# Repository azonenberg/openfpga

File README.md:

# openfpga
Open-source FPGA/CPLD toolchain project for multiple device families.

The most mature target is Silego GreenPAK4. Active work is underway for Xilinx CoolRunner-II and Cypress PSoC5LP.

Questions? Comments? Having trouble getting it to work? Join our IRC, ##openfpga on Freenode.

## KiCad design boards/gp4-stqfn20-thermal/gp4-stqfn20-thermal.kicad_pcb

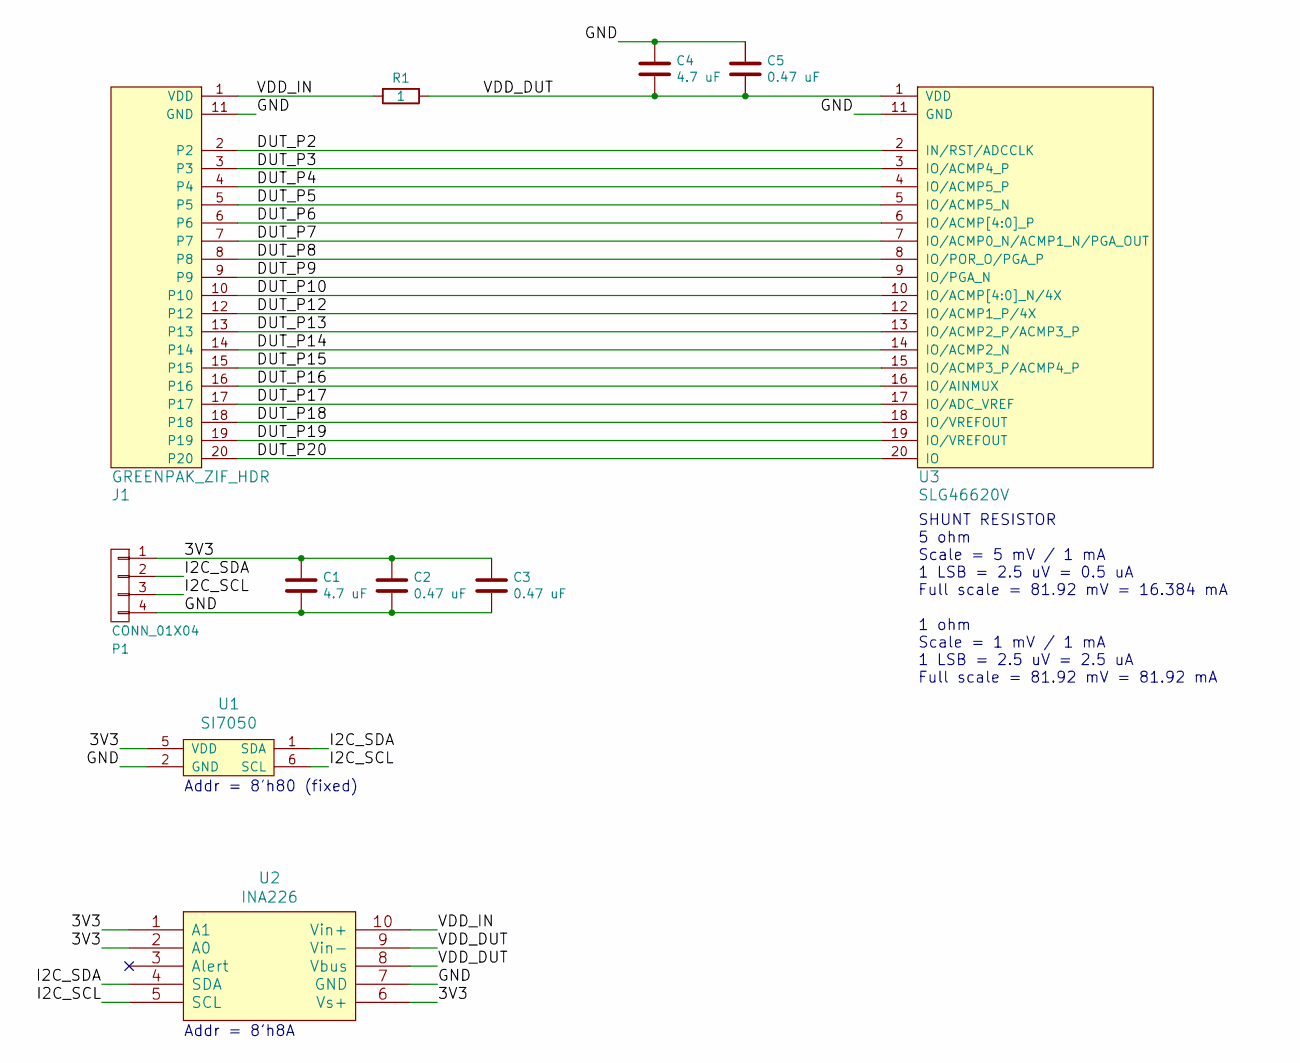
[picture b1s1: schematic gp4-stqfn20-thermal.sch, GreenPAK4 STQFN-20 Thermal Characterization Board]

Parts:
C1, C4: 4.7 uF; EIA_0603_CAP_NOSILK
C2, C3, C5: 0.47 uF; EIA_0402_CAP_NOSILK
J1: GREENPAK_ZIF_HDR; CONN_HEADER_2.54MM_2x10_RA_FEMALE
P1: CONN_01X04; CONN_HEADER_2.54MM_1x4
R1: 1; EIA_0805_CAP_NOSILK
U1: SI7050; DFN_6_1MM_3x3MM
U2: INA226; SOP_10_0.5MM_3MM
U3: SLG46620V; QFN_20_0.4MM_3x2MM_SILEGO_STQFN

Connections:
/3V3: C1.1, C2.1, C3.1, P1.1, U1.5 (VDD), U2.1 (A1), U2.2 (A0), U2.6 (Vs+)
/DUT_P2: J1.2, U3.2 (IN/RST/ADCCLK)
/DUT_P3: J1.3, U3.3 (IO/ACMP4_P)
/DUT_P4: J1.4, U3.4 (IO/ACMP5_P)
/DUT_P5: J1.5, U3.5 (IO/ACMP5_N)
/DUT_P6: J1.6, U3.6 (IO/ACMP[4:0]_P)
/DUT_P7: J1.7, U3.7 (IO/ACMP0_N/ACMP1_N/PGA_OUT)
/DUT_P8: J1.8, U3.8 (IO/POR_O/PGA_P)
/DUT_P9: J1.9, U3.9 (IO/PGA_N)
/DUT_P10: J1.10, U3.10 (IO/ACMP[4:0]_N/4X)
/DUT_P12: J1.12, U3.12 (IO/ACMP1_P/4X)
/DUT_P13: J1.13, U3.13 (IO/ACMP2_P/ACMP3_P)
/DUT_P14: J1.14, U3.14 (IO/ACMP2_N)
/DUT_P15: J1.15, U3.15 (IO/ACMP3_P/ACMP4_P)
/DUT_P16: J1.16, U3.16 (IO/AINMUX)
/DUT_P17: J1.17, U3.17 (IO/ADC_VREF)
/DUT_P18: J1.18, U3.18 (IO/VREFOUT)
/DUT_P19: J1.19, U3.19 (IO/VREFOUT)
/DUT_P20: J1.20, U3.20 (IO)
/GND: C1.2, C2.2, C3.2, C4.1, C5.1, J1.11 (GND), P1.4, U1.2 (GND), U2.7 (GND), U3.11 (GND)
/I2C_SCL: P1.3, U1.6 (SCL), U2.5 (SCL)
/I2C_SDA: P1.2, U1.1 (SDA), U2.4 (SDA)
/VDD_DUT: C4.2, C5.2, R1.1, U2.8 (Vbus), U2.9 (Vin-), U3.1 (VDD)
/VDD_IN: J1.1 (VDD), R1.2, U2.10 (Vin+)

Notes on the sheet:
Addr = 8'h80 (fixed)
Addr = 8'h8A
SHUNT RESISTOR 5 ohm Scale = 5 mV / 1 mA 1 LSB = 2.5 uV = 0.5 uA Full scale = 81.92 mV = 16.384 mA 1 ohm Scale = 1 mV / 1 mA 1 LSB = 2.5 uV = 2.5 uA Full scale = 81.92 mV = 81.92 mA

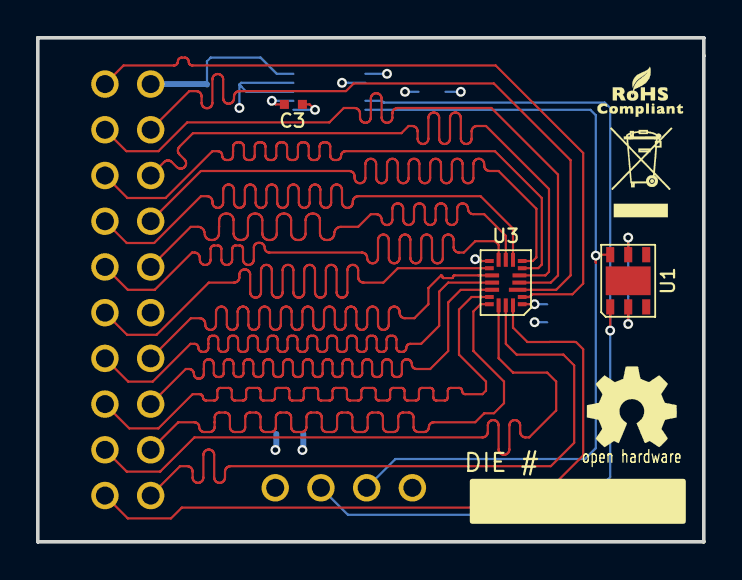
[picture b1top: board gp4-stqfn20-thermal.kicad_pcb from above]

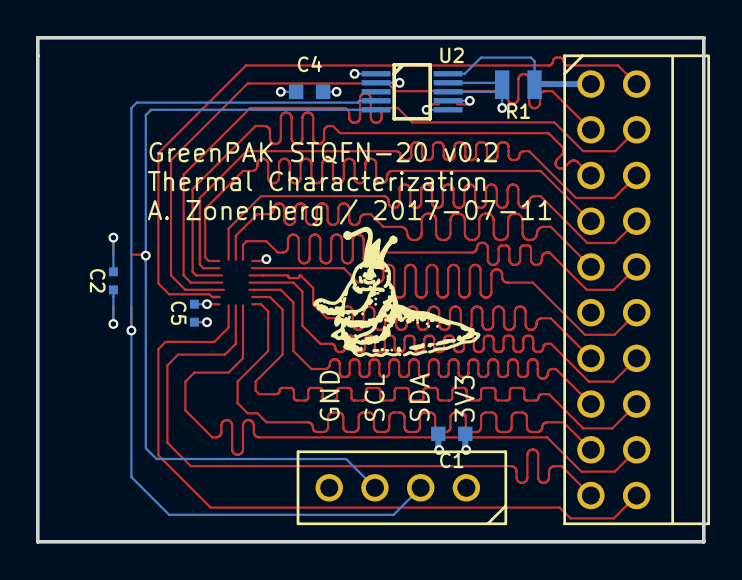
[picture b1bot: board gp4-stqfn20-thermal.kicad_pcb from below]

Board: 4 copper layers, 37.0 x 28.0 mm, 11 parts (8 on the bottom side), 24 nets.

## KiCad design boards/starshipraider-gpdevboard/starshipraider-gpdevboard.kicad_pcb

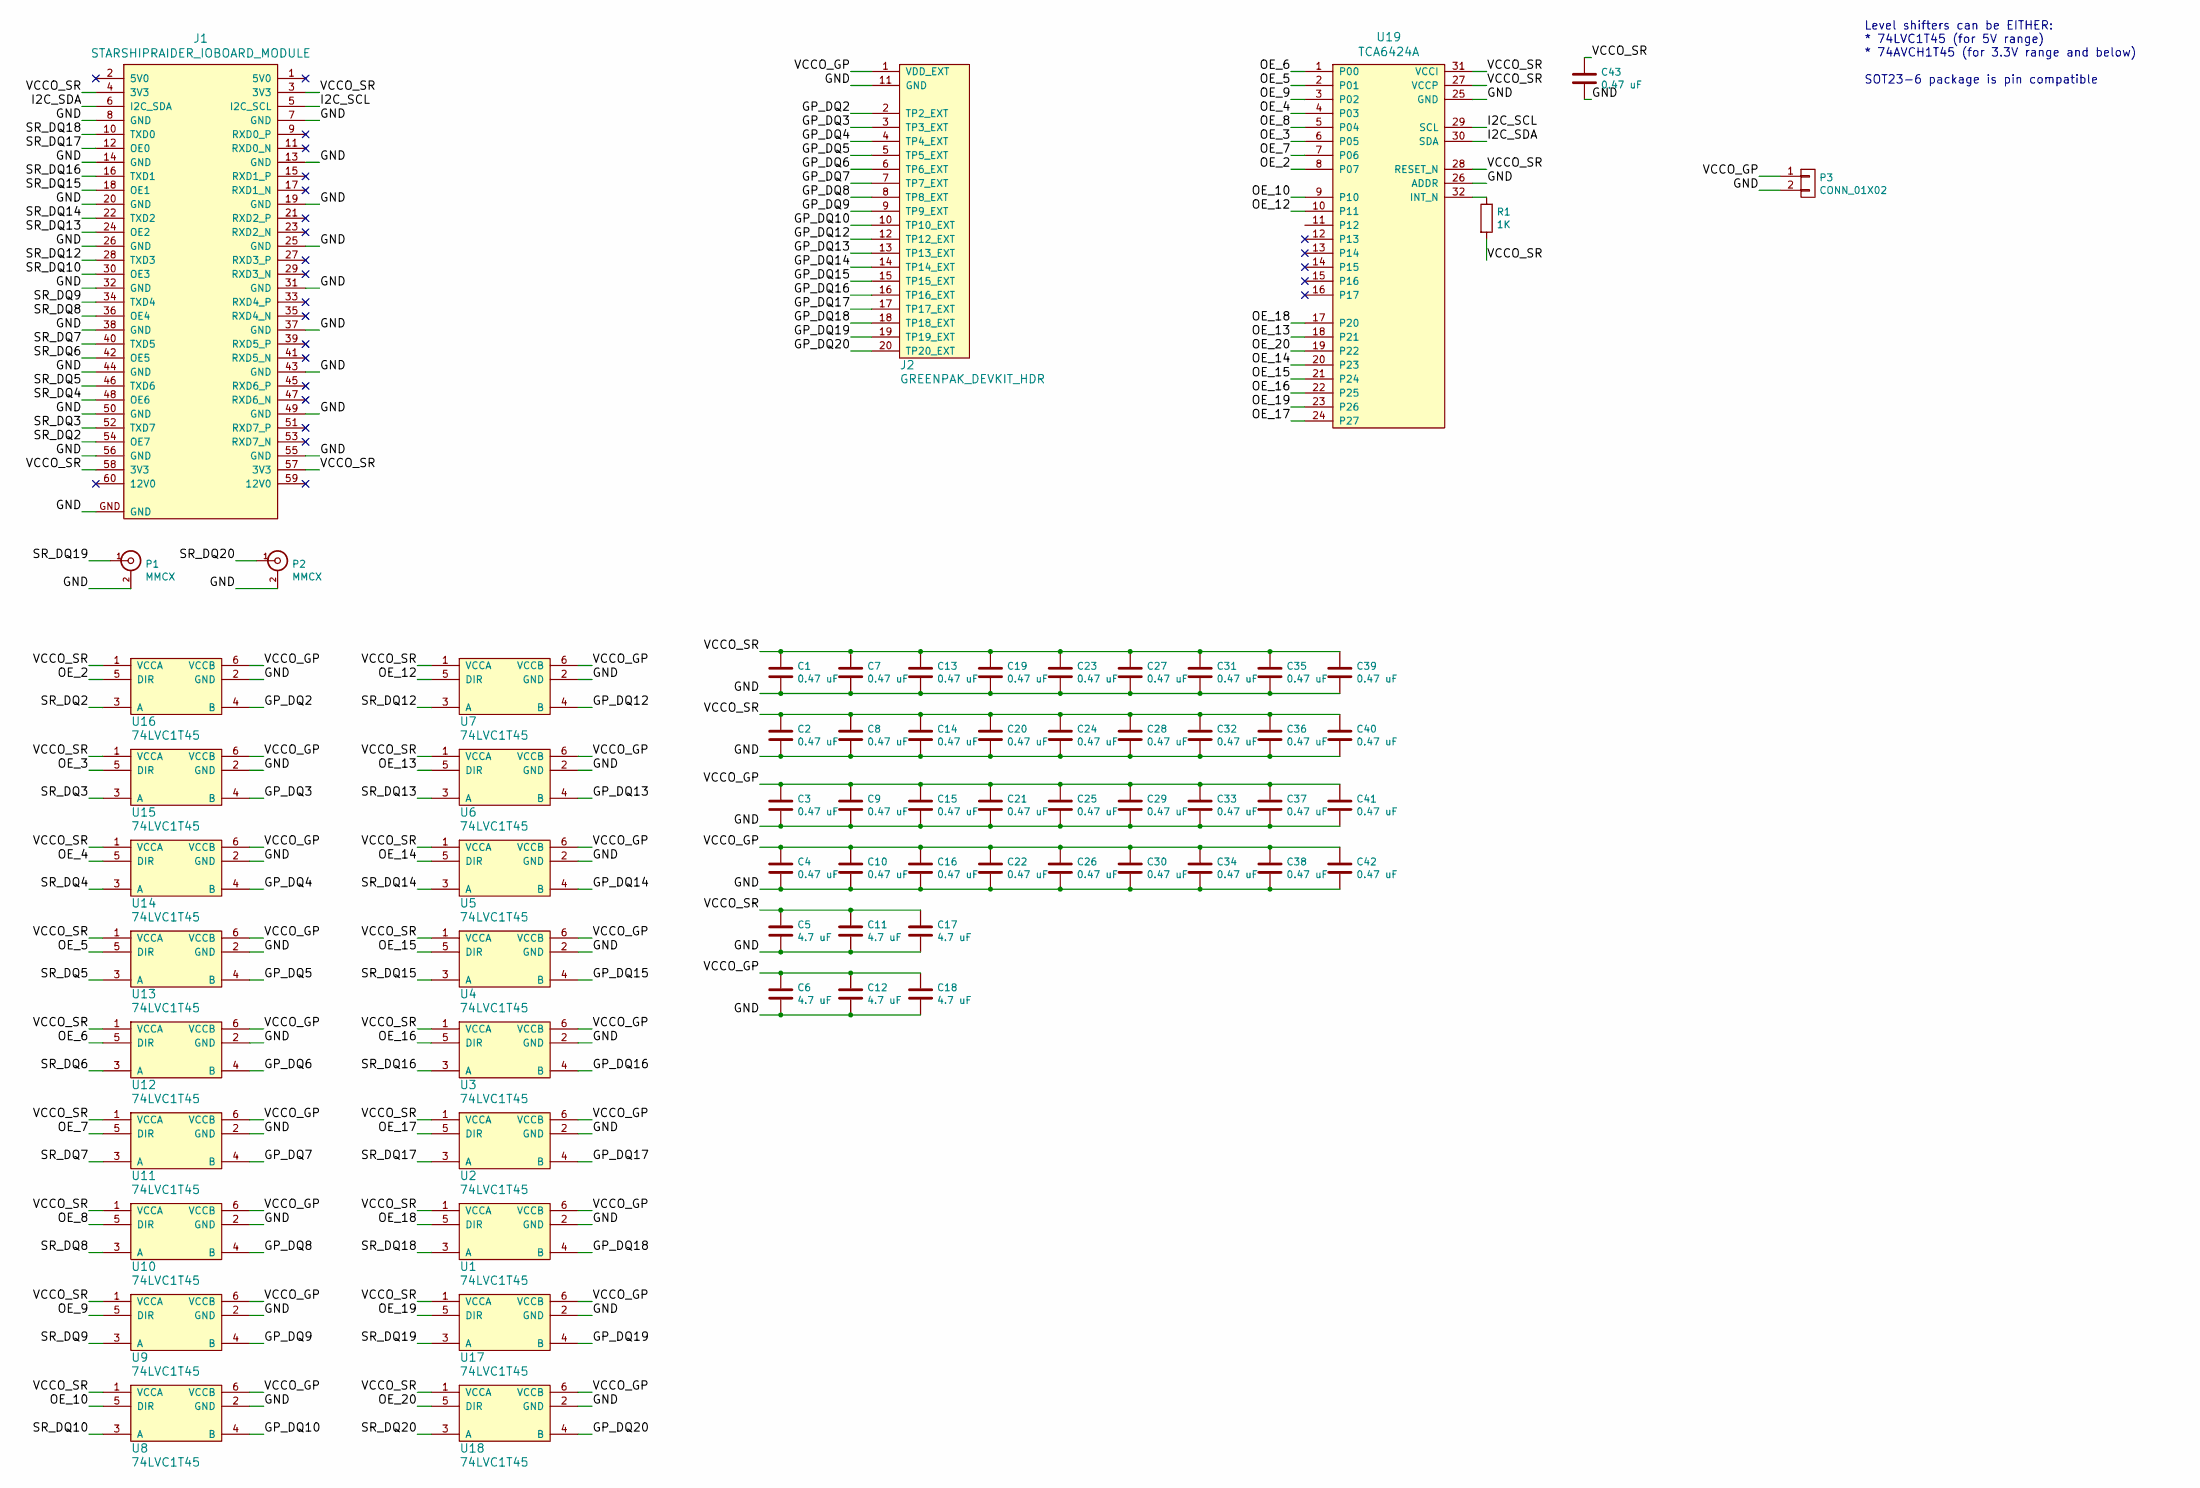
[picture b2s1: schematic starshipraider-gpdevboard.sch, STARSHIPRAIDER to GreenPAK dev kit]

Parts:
C1, C2, C3, C4, C7, C8, C9, C10, C13, C14, C15, C16, C19, C20, C21, C22, C23, C24, C25, C26, C27, C28, C29, C30, C31, C32, C33, C34, C35, C36, C37, C38, C39, C40, C41, C42, C43: 0.47 uF; EIA_0402_CAP_NOSILK
C5, C6, C11, C12, C17, C18: 4.7 uF; EIA_0603_CAP_NOSILK
J1: STARSHIPRAIDER_IOBOARD_MODULE; CONN_SAMTEC_QSH-030-01-L-D-A
J2: GREENPAK_DEVKIT_HDR; CONN_HEADER_2.54MM_2x10_RA_FEMALE
P1, P2: MMCX; CONN_MMCX_LINX_CONNMMCX002SMD
P3: CONN_01X02; CONN_HEADER_2.54MM_1x2
R1: 1K; EIA_0402_RES_NOSILK
U1, U2, U3, U4, U5, U6, U7, U8, U9, U10, U11, U12, U13, U14, U15, U16, U17, U18: 74LVC1T45; SOT23_6
U19: TCA6424A; QFN_32_0.5MM_5x5MM

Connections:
/GND: C1.2, C2.2, C3.2, C4.2, C5.2, C6.2, C7.2, C8.2, C9.2, C10.2, C11.2, C12.2, C13.2, C14.2, C15.2, C16.2, C17.2, C18.2, C19.2, C20.2, C21.2, C22.2, C23.2, C24.2, C25.2, C26.2, C27.2, C28.2, C29.2, C30.2, C31.2, C32.2, C33.2, C34.2, C35.2, C36.2, C37.2, C38.2, C39.2, C40.2, C41.2, C42.2, C43.2, J1.7 (GND), J1.8 (GND), J1.13 (GND), J1.14 (GND), J1.19 (GND), J1.20 (GND), J1.25 (GND), J1.26 (GND), J1.31 (GND), J1.32 (GND), J1.37 (GND), J1.38 (GND), J1.43 (GND), J1.44 (GND), J1.49 (GND), J1.50 (GND), J1.55 (GND), J1.56 (GND), J1.GND, J2.11 (GND), P1.2 (Ext), P2.2 (Ext), P3.2, U1.2 (GND), U2.2 (GND), U3.2 (GND), U4.2 (GND), U5.2 (GND), U6.2 (GND), U7.2 (GND), U8.2 (GND), U9.2 (GND), U10.2 (GND), U11.2 (GND), U12.2 (GND), U13.2 (GND), U14.2 (GND), U15.2 (GND), U16.2 (GND), U17.2 (GND), U18.2 (GND), U19.25 (GND), U19.26 (ADDR)
/GP_DQ2: J2.2 (TP2_EXT), U16.4 (B)
/GP_DQ3: J2.3 (TP3_EXT), U15.4 (B)
/GP_DQ4: J2.4 (TP4_EXT), U14.4 (B)
/GP_DQ5: J2.5 (TP5_EXT), U13.4 (B)
/GP_DQ6: J2.6 (TP6_EXT), U12.4 (B)
/GP_DQ7: J2.7 (TP7_EXT), U11.4 (B)
/GP_DQ8: J2.8 (TP8_EXT), U10.4 (B)
/GP_DQ9: J2.9 (TP9_EXT), U9.4 (B)
/GP_DQ10: J2.10 (TP10_EXT), U8.4 (B)
/GP_DQ12: J2.12 (TP12_EXT), U7.4 (B)
/GP_DQ13: J2.13 (TP13_EXT), U6.4 (B)
/GP_DQ14: J2.14 (TP14_EXT), U5.4 (B)
/GP_DQ15: J2.15 (TP15_EXT), U4.4 (B)
/GP_DQ16: J2.16 (TP16_EXT), U3.4 (B)
/GP_DQ17: J2.17 (TP17_EXT), U2.4 (B)
/GP_DQ18: J2.18 (TP18_EXT), U1.4 (B)
/GP_DQ19: J2.19 (TP19_EXT), U17.4 (B)
/GP_DQ20: J2.20 (TP20_EXT), U18.4 (B)
/I2C_SCL: J1.5 (I2C_SCL), U19.29 (SCL)
/I2C_SDA: J1.6 (I2C_SDA), U19.30 (SDA)
/OE_2: U16.5 (DIR), U19.8 (P07)
/OE_3: U15.5 (DIR), U19.6 (P05)
/OE_4: U14.5 (DIR), U19.4 (P03)
/OE_5: U13.5 (DIR), U19.2 (P01)
/OE_6: U12.5 (DIR), U19.1 (P00)
/OE_7: U11.5 (DIR), U19.7 (P06)
/OE_8: U10.5 (DIR), U19.5 (P04)
/OE_9: U9.5 (DIR), U19.3 (P02)
/OE_10: U8.5 (DIR), U19.9 (P10)
/OE_12: U7.5 (DIR), U19.10 (P11)
/OE_13: U6.5 (DIR), U19.18 (P21)
/OE_14: U5.5 (DIR), U19.20 (P23)
/OE_15: U4.5 (DIR), U19.21 (P24)
/OE_16: U3.5 (DIR), U19.22 (P25)
/OE_17: U2.5 (DIR), U19.24 (P27)
/OE_18: U1.5 (DIR), U19.17 (P20)
/OE_19: U17.5 (DIR), U19.23 (P26)
/OE_20: U18.5 (DIR), U19.19 (P22)
/SR_DQ2: J1.54 (OE7), U16.3 (A)
/SR_DQ3: J1.52 (TXD7), U15.3 (A)
/SR_DQ4: J1.48 (OE6), U14.3 (A)
/SR_DQ5: J1.46 (TXD6), U13.3 (A)
/SR_DQ6: J1.42 (OE5), U12.3 (A)
/SR_DQ7: J1.40 (TXD5), U11.3 (A)
/SR_DQ8: J1.36 (OE4), U10.3 (A)
/SR_DQ9: J1.34 (TXD4), U9.3 (A)
/SR_DQ10: J1.30 (OE3), U8.3 (A)
/SR_DQ12: J1.28 (TXD3), U7.3 (A)
/SR_DQ13: J1.24 (OE2), U6.3 (A)
/SR_DQ14: J1.22 (TXD2), U5.3 (A)
/SR_DQ15: J1.18 (OE1), U4.3 (A)
/SR_DQ16: J1.16 (TXD1), U3.3 (A)
/SR_DQ17: J1.12 (OE0), U2.3 (A)
/SR_DQ18: J1.10 (TXD0), U1.3 (A)
/SR_DQ19: P1.1 (In), U17.3 (A)
/SR_DQ20: P2.1 (In), U18.3 (A)
/VCCO_GP: C3.1, C4.1, C6.1, C9.1, C10.1, C12.1, C15.1, C16.1, C18.1, C21.1, C22.1, C25.1, C26.1, C29.1, C30.1, C33.1, C34.1, C37.1, C38.1, C41.1, C42.1, J2.1 (VDD_EXT), P3.1, U1.6 (VCCB), U2.6 (VCCB), U3.6 (VCCB), U4.6 (VCCB), U5.6 (VCCB), U6.6 (VCCB), U7.6 (VCCB), U8.6 (VCCB), U9.6 (VCCB), U10.6 (VCCB), U11.6 (VCCB), U12.6 (VCCB), U13.6 (VCCB), U14.6 (VCCB), U15.6 (VCCB), U16.6 (VCCB), U17.6 (VCCB), U18.6 (VCCB)
/VCCO_SR: C1.1, C2.1, C5.1, C7.1, C8.1, C11.1, C13.1, C14.1, C17.1, C19.1, C20.1, C23.1, C24.1, C27.1, C28.1, C31.1, C32.1, C35.1, C36.1, C39.1, C40.1, C43.1, J1.3 (3V3), J1.4 (3V3), J1.57 (3V3), J1.58 (3V3), R1.2, U1.1 (VCCA), U2.1 (VCCA), U3.1 (VCCA), U4.1 (VCCA), U5.1 (VCCA), U6.1 (VCCA), U7.1 (VCCA), U8.1 (VCCA), U9.1 (VCCA), U10.1 (VCCA), U11.1 (VCCA), U12.1 (VCCA), U13.1 (VCCA), U14.1 (VCCA), U15.1 (VCCA), U16.1 (VCCA), U17.1 (VCCA), U18.1 (VCCA), U19.27 (VCCP), U19.28 (RESET_N), U19.31 (VCCI)
unnamed: R1.1, U19.32 (INT_N)

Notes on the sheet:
Level shifters can be EITHER: * 74LVC1T45 (for 5V range) * 74AVCH1T45 (for 3.3V range and below) SOT23-6 package is pin compatible

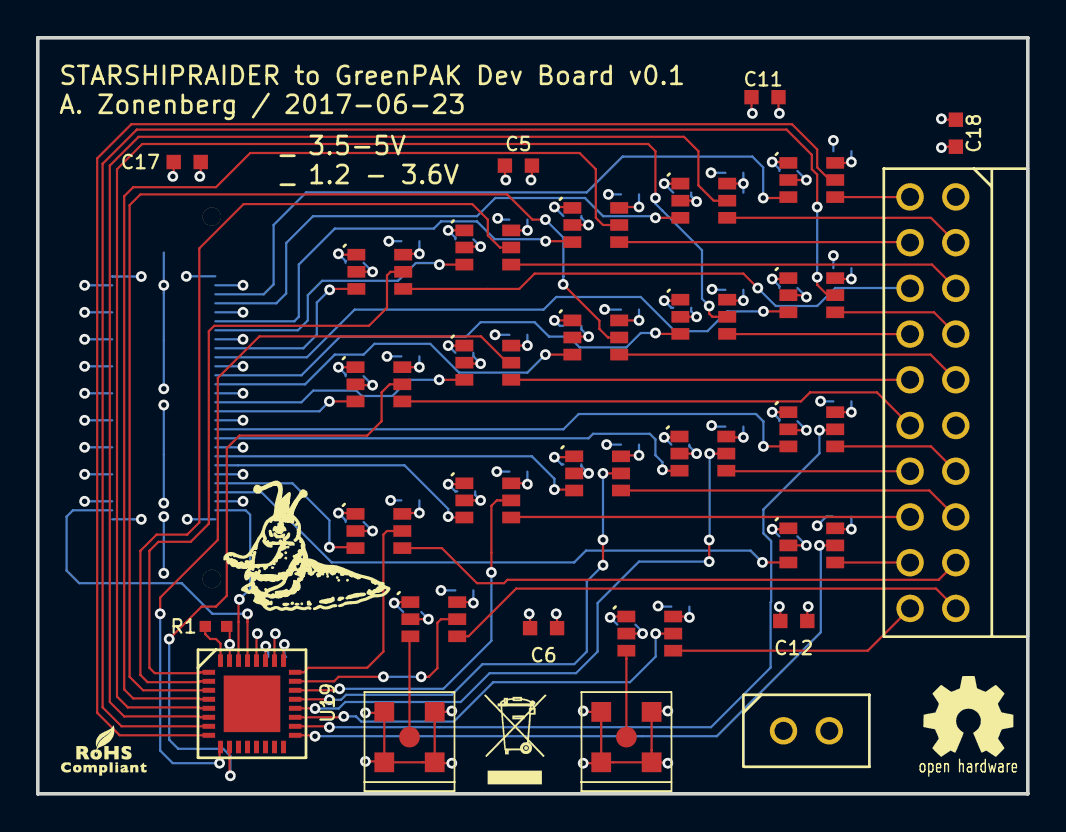
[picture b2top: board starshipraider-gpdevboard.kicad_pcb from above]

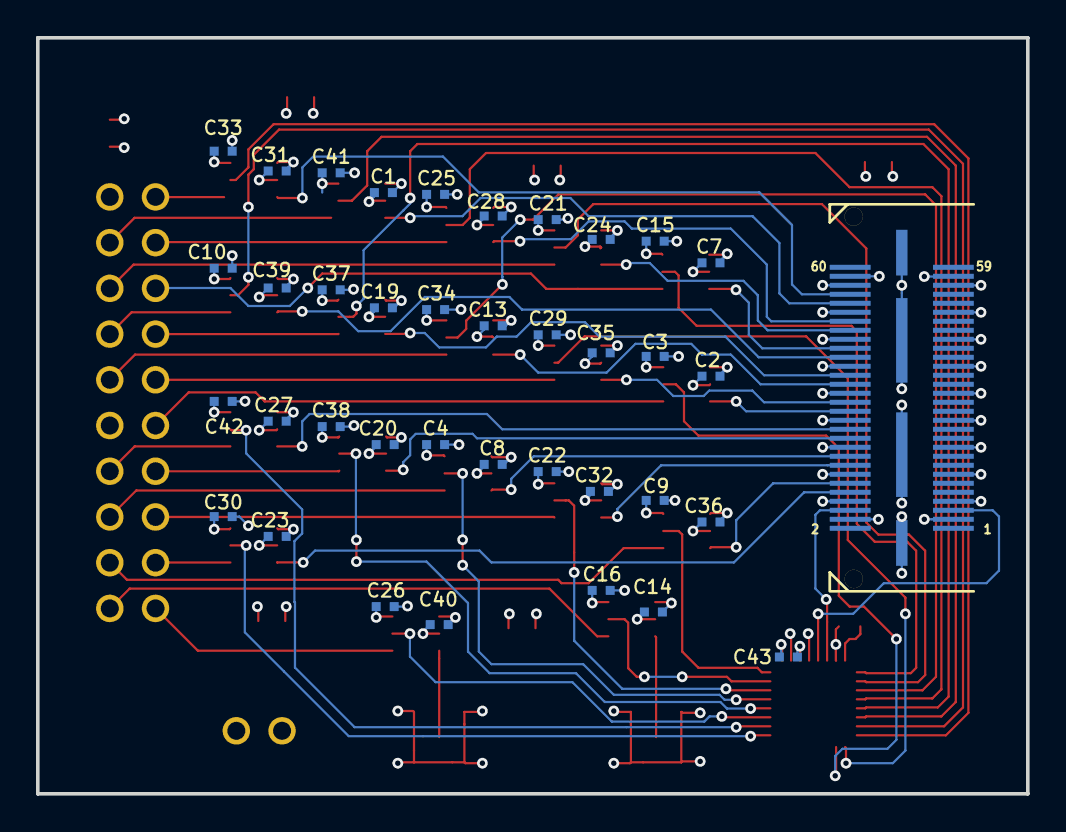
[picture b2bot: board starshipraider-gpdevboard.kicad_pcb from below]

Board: 4 copper layers, 55.0 x 42.0 mm, 68 parts (38 on the bottom side), 60 nets.

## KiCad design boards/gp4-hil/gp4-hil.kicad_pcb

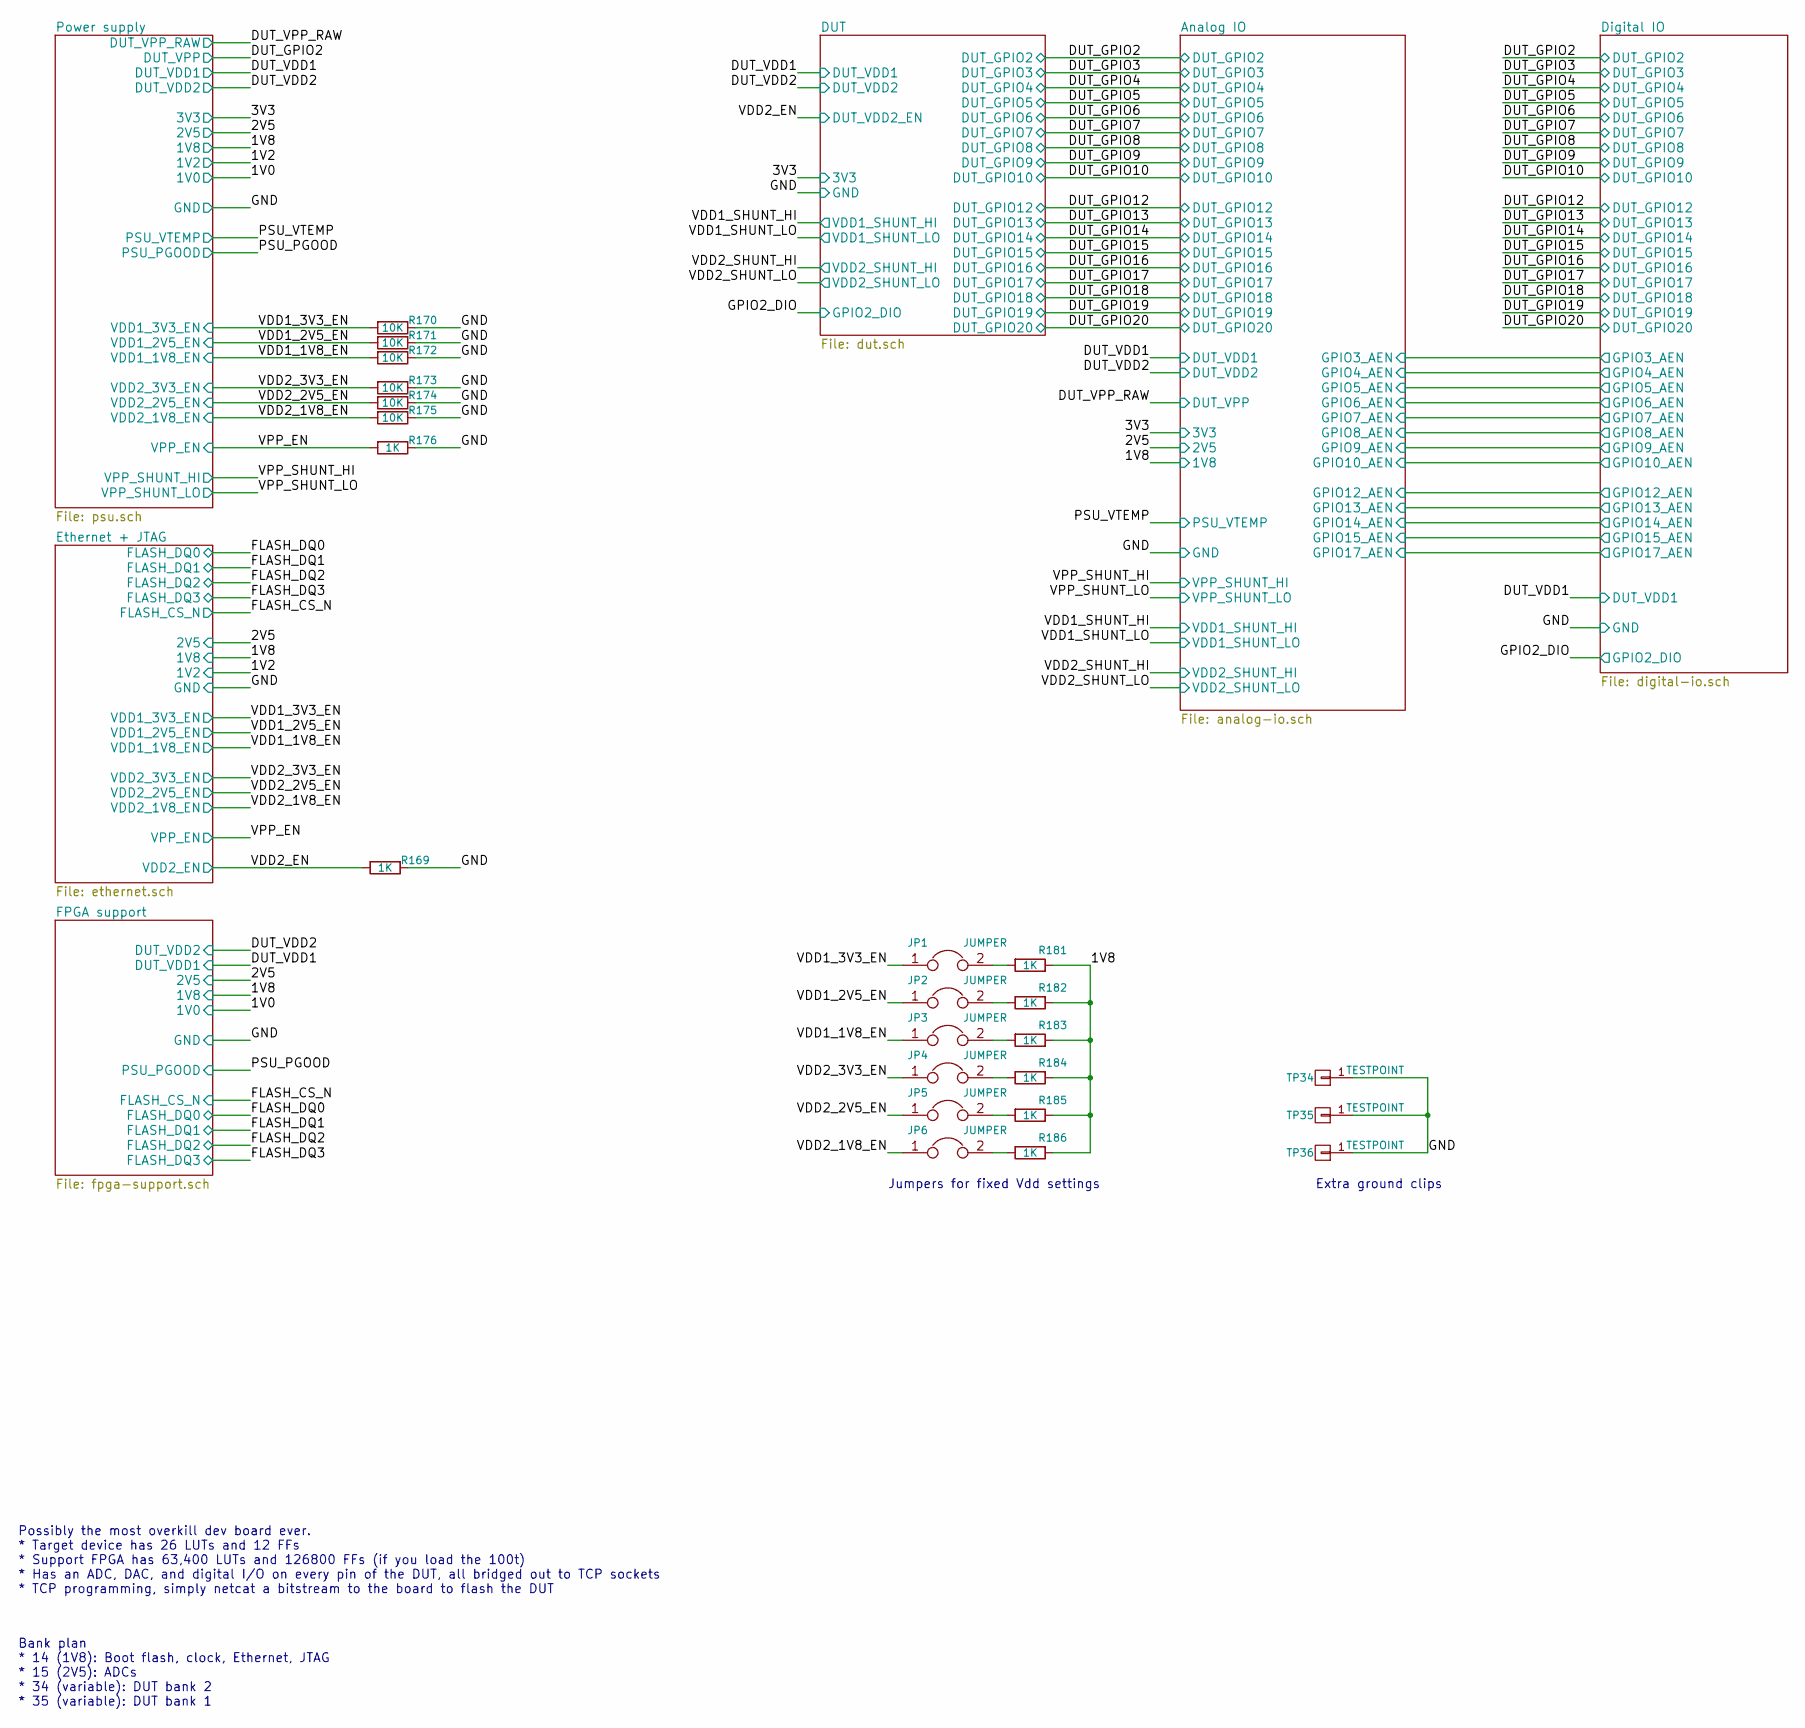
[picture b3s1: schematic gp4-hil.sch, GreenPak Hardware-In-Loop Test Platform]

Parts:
JP1, JP2, JP3, JP4, JP5, JP6: JUMPER; JUMPER_2.54MM_2POS
R169, R176, R181, R182, R183, R184, R185, R186: 1K; EIA_0402_RES_NOSILK
R170, R171, R172, R173, R174, R175: 10K; EIA_0402_RES_NOSILK
TP34, TP35, TP36: TESTPOINT; TESTPOINT_SMT_KEYSTONE_5016

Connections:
/Analog IO/1V8: R181.1, R182.1, R183.1, R184.1, R185.1, R186.1; also elsewhere on the board
/Analog IO/GND: R169.1, R170.1, R171.1, R172.1, R173.1, R174.1, R175.1, R176.1, TP34.1, TP35.1, TP36.1; also elsewhere on the board
/DUT/DUT_VDD2_EN: R169.2; also elsewhere on the board
/Ethernet + JTAG/VDD1_1V8_EN: JP3.1, R172.2; also elsewhere on the board
/Ethernet + JTAG/VDD1_2V5_EN: JP2.1, R171.2; also elsewhere on the board
/Ethernet + JTAG/VDD1_3V3_EN: JP1.1, R170.2; also elsewhere on the board
/Ethernet + JTAG/VDD2_1V8_EN: JP6.1, R175.2; also elsewhere on the board
/Ethernet + JTAG/VDD2_2V5_EN: JP5.1, R174.2; also elsewhere on the board
/Ethernet + JTAG/VDD2_3V3_EN: JP4.1, R173.2; also elsewhere on the board
/Ethernet + JTAG/VPP_EN: R176.2; also elsewhere on the board
unnamed: JP1.2, R181.2
unnamed: JP2.2, R182.2
unnamed: JP3.2, R183.2
unnamed: JP4.2, R184.2
unnamed: JP5.2, R185.2
unnamed: JP6.2, R186.2

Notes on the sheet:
Bank plan * 14 (1V8): Boot flash, clock, Ethernet, JTAG * 15 (2V5): ADCs * 34 (variable): DUT bank 2 * 35 (variable): DUT bank 1
Possibly the most overkill dev board ever. * Target device has 26 LUTs and 12 FFs * Support FPGA has 63,400 LUTs and 126800 FFs (if you load the 100t) * Has an ADC, DAC, and digital I/O on every pin of the DUT, all bridged out to TCP sockets * TCP programming, simply netcat a bitstream to the board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
Jumpers for fixed Vdd settings
Extra ground clips
